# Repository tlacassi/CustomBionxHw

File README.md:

# Custom BionX hardware

The original battery of my BionX e-bike is worn out. The new pack gets a DALY BMS with
balancing, and these boards replace what the original electronics did besides battery management.
Firmware: [BIONX_console_ESP32](https://github.com/tlacassi/BIONX_console_ESP32).

## How it works

Two ESP32-S3 boards linked by the bike's CAN bus.

- **Power Control** (near the battery): drives the motor, handles precharge, switching,
  sleep, current/voltage measurement and the link to the BMS.
- **Display** (handlebar): round screen, rotary encoder, brake and throttle inputs.

## Status

In progress.

- Power Control: routed (112 × 82 mm, 4 layers), **not manufactured yet**.
  The [audit](docs/AUDIT_PCB_POWER_CONTROL.md) (in French) lists issues to fix before ordering.
- Display: schematic only.

Designed in KiCad 10. Design choices and BOM in [`docs/`](docs/).

> Unvalidated prototype: do not manufacture or connect to a battery as is.

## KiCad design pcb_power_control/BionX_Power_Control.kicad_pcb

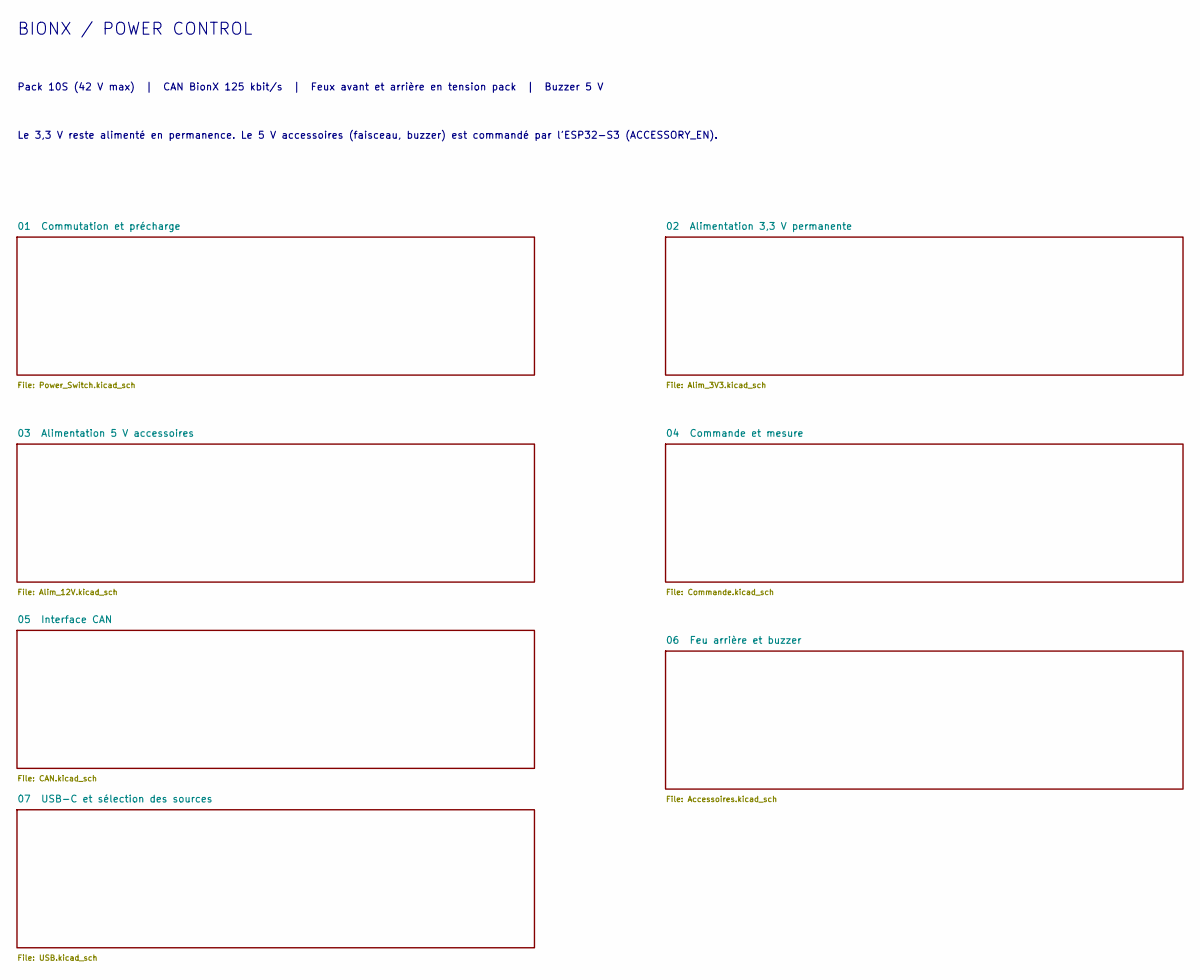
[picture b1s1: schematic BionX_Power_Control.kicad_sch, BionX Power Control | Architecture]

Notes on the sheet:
BIONX / POWER CONTROL
Pack 10S (42 V max) | CAN BionX 125 kbit/s | Feux avant et arrière en tension pack | Buzzer 5 V
Le 3,3 V reste alimenté en permanence. Le 5 V accessoires (faisceau, buzzer) est commandé par l'ESP32-S3 (ACCESSORY_EN).

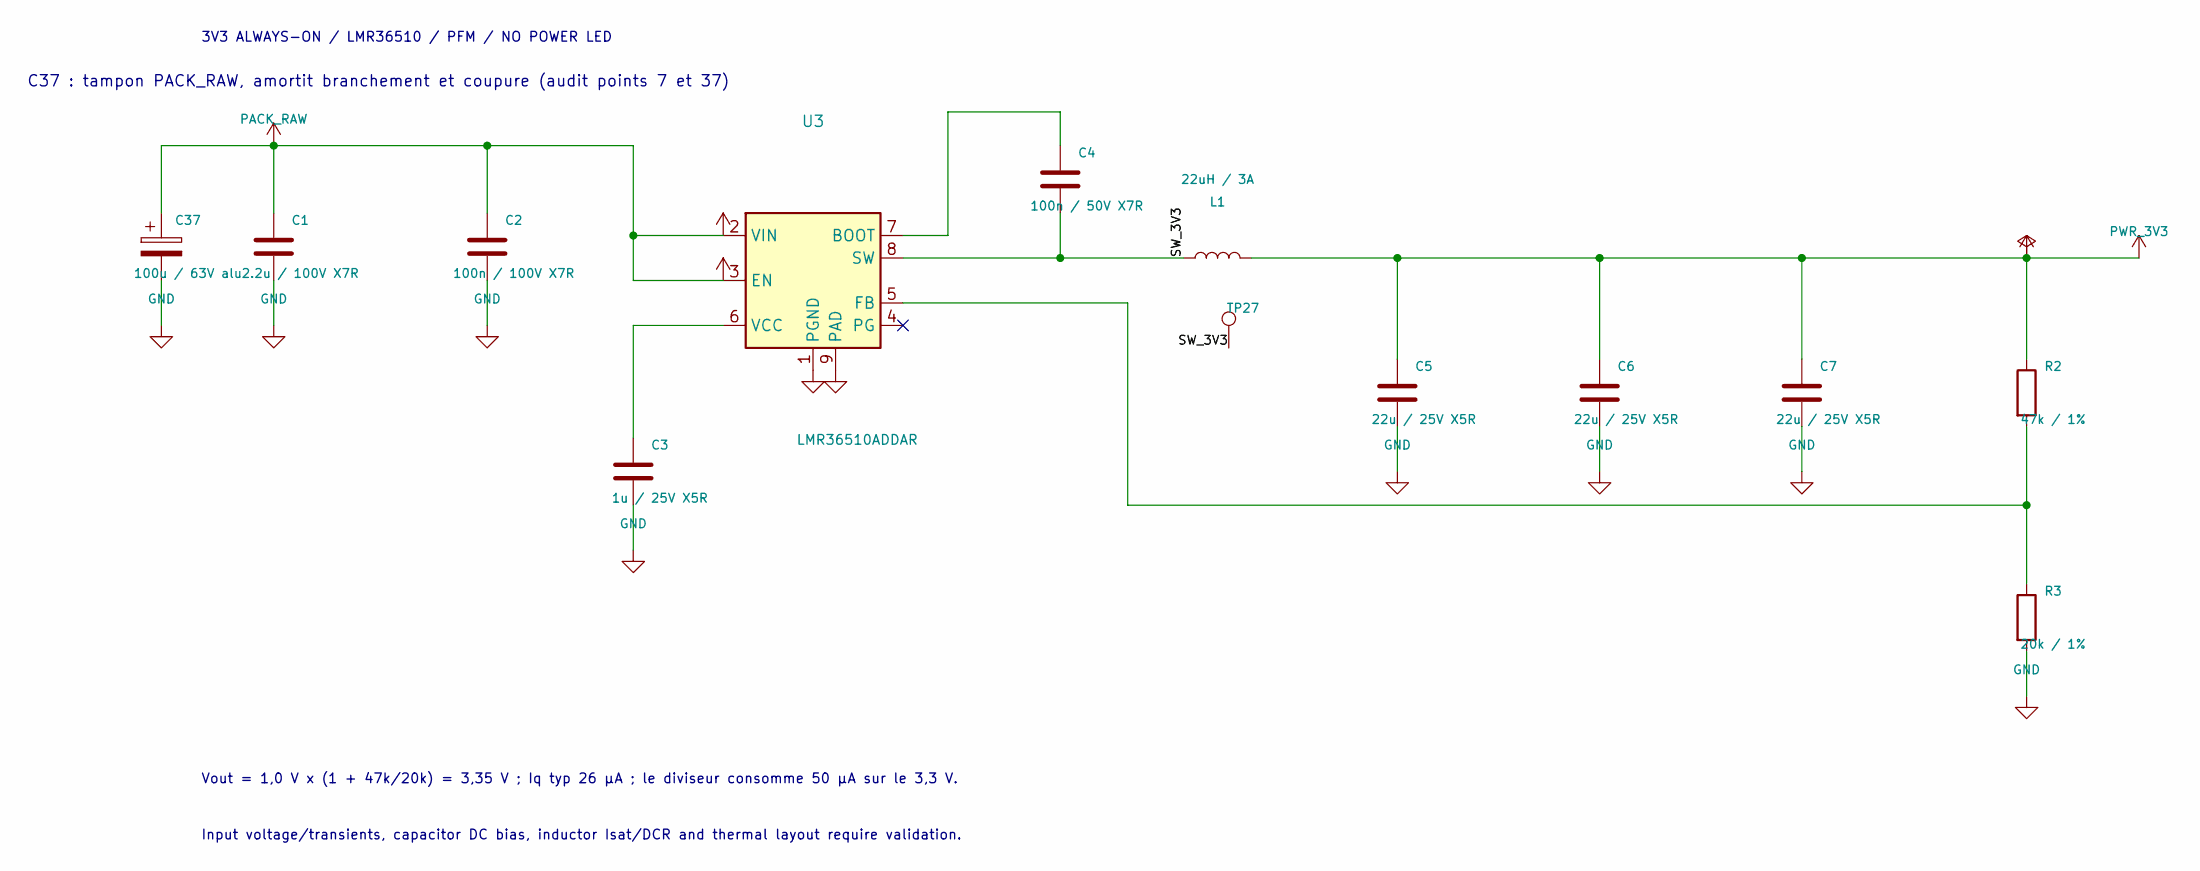
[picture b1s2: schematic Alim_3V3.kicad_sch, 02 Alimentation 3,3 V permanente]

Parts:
C1: 2.2u / 100V X7R; C_1210_3225Metric; MPN CL32B225KCJSNNE; LCSC C55151
C2: 100n / 100V X7R; C_0805_2012Metric; MPN CL21B104KCC5PNC; LCSC C472809
C3: 1u / 25V X5R; C_0402_1005Metric; MPN CL05A105KA5NQNC; LCSC C52923
C4: 100n / 50V X7R; C_0402_1005Metric; MPN CL05B104KB54PNC; LCSC C307331
C5, C6, C7: 22u / 25V X5R; C_1206_3216Metric; MPN CL31A226KAHNNNE; LCSC C12891
C37: 100u / 63V alu; CP_Elec_10x10.5; MPN CS1J101M-CRG10; LCSC C116430
L1: 22uH / 3A; L_Changjiang_FXL0630; MPN SRG0630-220-M; LCSC C53462993
R2: 47k / 1%; R_0603_1608Metric; MPN 0603WAF4702T5E; LCSC C25819
R3: 20k / 1%; R_0603_1608Metric; MPN 0603WAF2002T5E; LCSC C4184
TP27: SW_3V3; TestPoint_Pad_D1.0mm
U3: LMR36510ADDAR; HSOP-8-1EP_3.9x4.9mm_P1.27mm_EP2.41x3.1mm; MPN LMR36510ADDAR; LCSC C1858393

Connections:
/02 Alimentation 3,3 V permanente/SW_3V3: C4.2, L1.1, TP27.1, U3.8 (SW)
unnamed: C4.1, U3.7 (BOOT)
unnamed: R2.2, R3.1, U3.5 (FB)
unnamed: C3.1, U3.6 (VCC)
PWR_3V3: C5.1, C6.1, C7.1, L1.2, R2.1; also elsewhere on the board

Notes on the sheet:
Vout = 1,0 V x (1 + 47k/20k) = 3,35 V ; Iq typ 26 µA ; le diviseur consomme 50 µA sur le 3,3 V.
3V3 ALWAYS-ON / LMR36510 / PFM / NO POWER LED
Input voltage/transients, capacitor DC bias, inductor Isat/DCR and thermal layout require validation.
C37 : tampon PACK_RAW, amortit branchement et coupure (audit points 7 et 37)

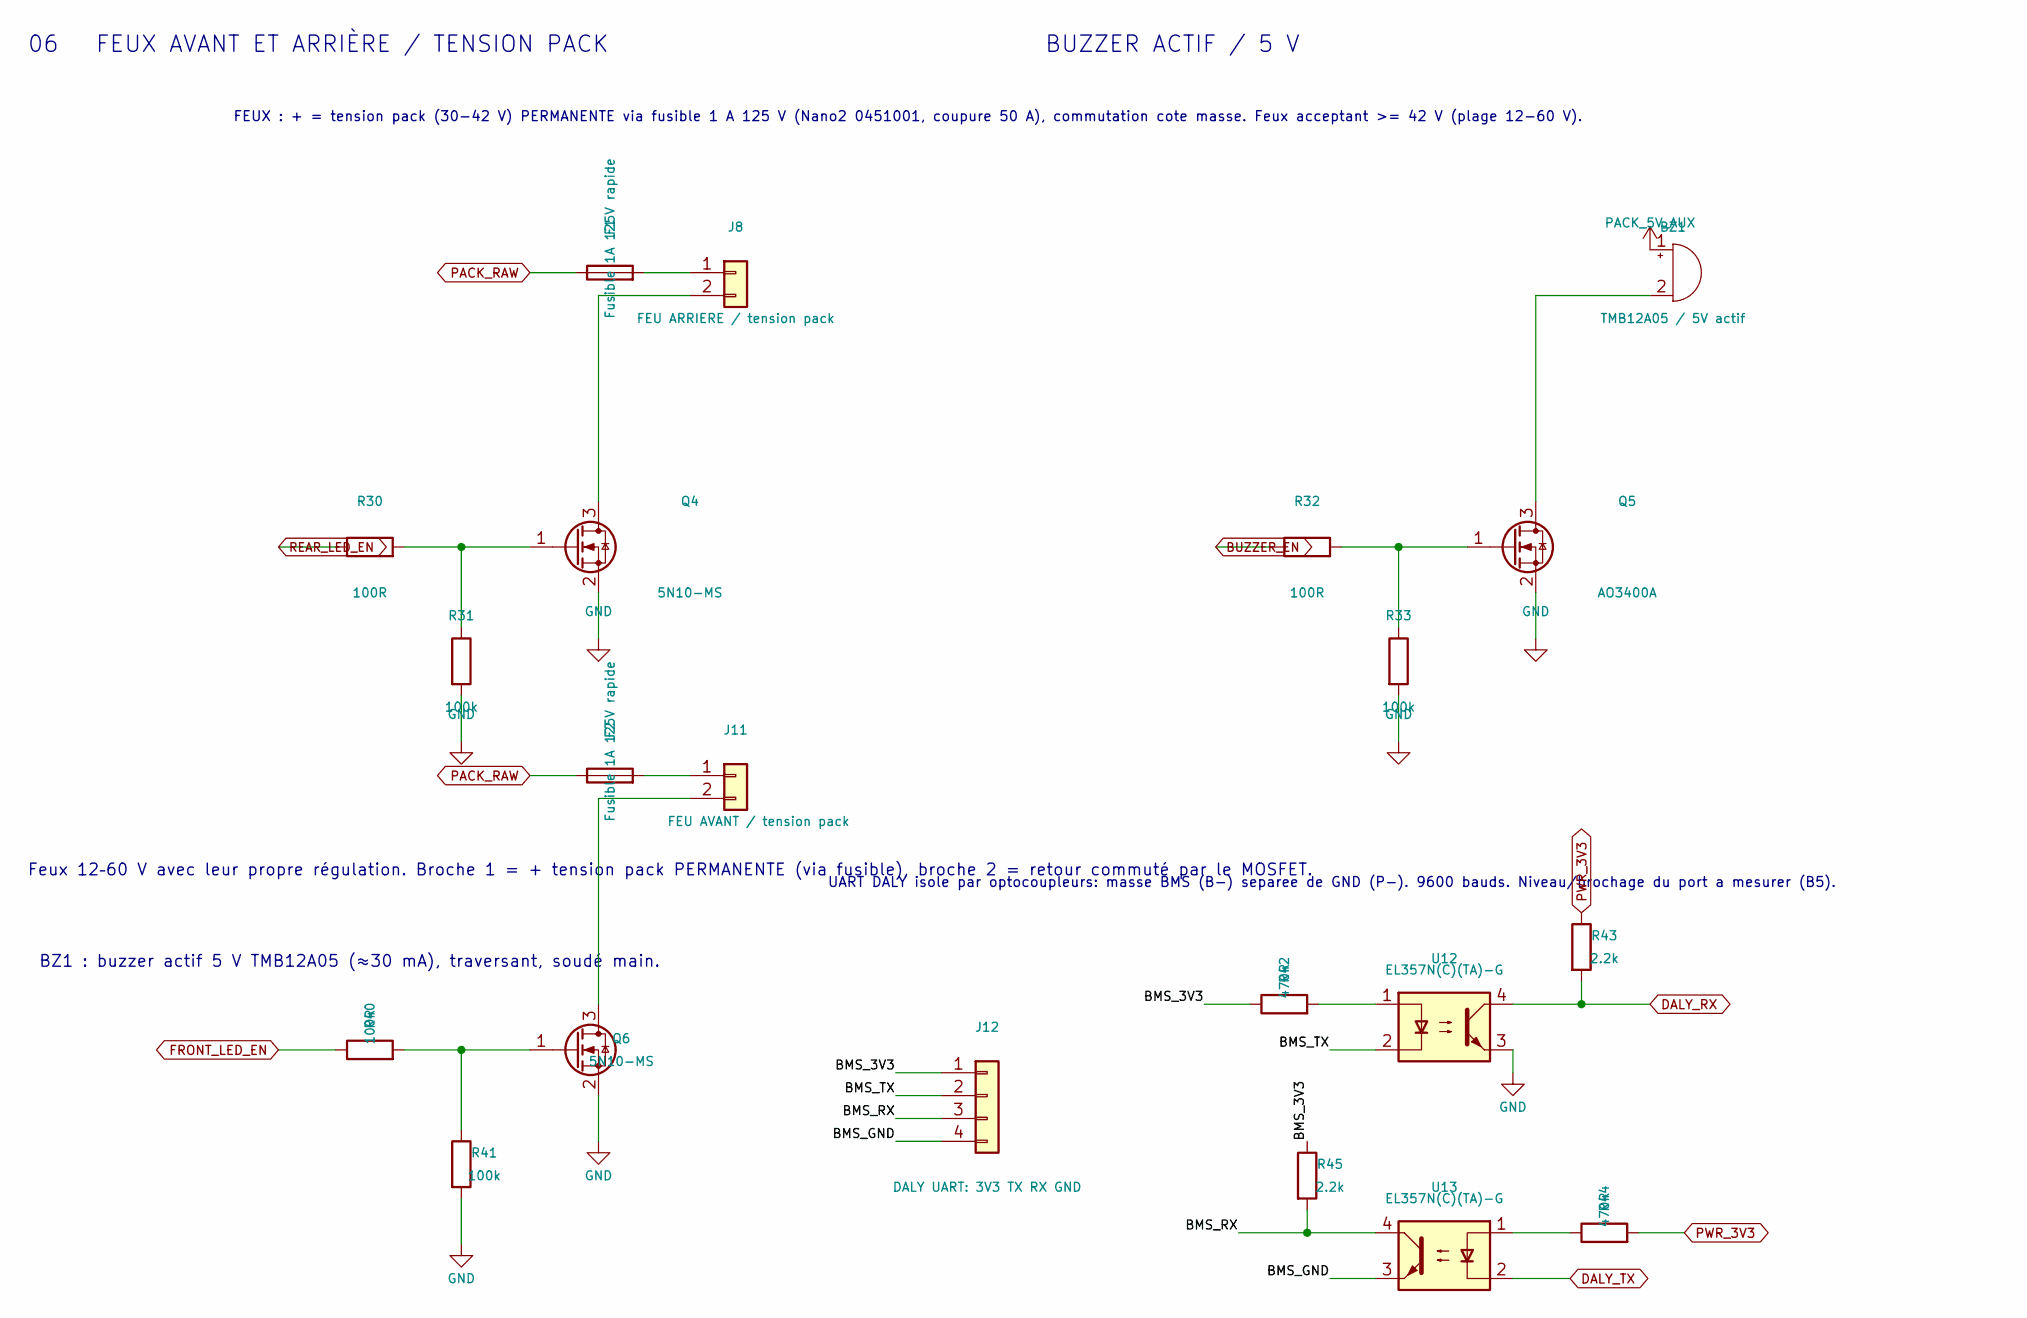
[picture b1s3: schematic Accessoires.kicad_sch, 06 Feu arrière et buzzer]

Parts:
BZ1: TMB12A05 / 5V actif; Buzzer_12x9.5RM7.6; MPN TMB12A05
F1, F2: Fusible 1A 125V rapide; Fuse_Littelfuse-NANO2-451_453; MPN 0451001.MRL; LCSC C3099
J8: FEU ARRIERE / tension pack; JST_XH_B2B-XH-A_1x02_P2.50mm_Vertical; MPN B2B-XH-A
J11: FEU AVANT / tension pack; JST_XH_B2B-XH-A_1x02_P2.50mm_Vertical; MPN B2B-XH-A
J12: DALY UART: 3V3 TX RX GND; JST_XH_B4B-XH-A_1x04_P2.50mm_Vertical; MPN B4B-XH-A
Q4, Q6: 5N10-MS; SOT-23; MPN 5N10-MS; LCSC C5140036
Q5: AO3400A; SOT-23; MPN AO3400A; LCSC C20917
R30, R32, R40: 100R; R_0603_1608Metric; MPN 0603WAF1000T5E; LCSC C22775
R31, R33, R41: 100k; R_0603_1608Metric; MPN 0603WAF1003T5E; LCSC C25803
R42, R44: 470R; R_0603_1608Metric; MPN 0603WAF4700T5E; LCSC C23179
R43, R45: 2.2k; R_0603_1608Metric; MPN 0603WAF2201T5E; LCSC C4190
U12, U13: EL357N(C)(TA)-G; SOP-4_EL357N_Everlight; MPN EL357N(C)(TA)-G; LCSC C42379244

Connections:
/06 Feu arrière et buzzer/BMS_3V3: J12.1, R42.1, R45.1
/06 Feu arrière et buzzer/BMS_GND: J12.4, U13.3
/06 Feu arrière et buzzer/BMS_RX: J12.3, R45.2, U13.4
/06 Feu arrière et buzzer/BMS_TX: J12.2, U12.2
BUZZER_EN: R32.1; also elsewhere on the board
DALY_RX: R43.2, U12.4; also elsewhere on the board
DALY_TX: U13.2; also elsewhere on the board
FRONT_LED_EN: R40.1; also elsewhere on the board
unnamed: BZ1.2 (-), Q5.3 (D)
unnamed: F1.2, J8.1
unnamed: J8.2, Q4.3 (D)
unnamed: F2.2, J11.1
unnamed: J11.2, Q6.3 (D)
unnamed: Q4.1 (G), R30.2, R31.1
unnamed: Q5.1 (G), R32.2, R33.1
unnamed: Q6.1 (G), R40.2, R41.1
unnamed: R42.2, U12.1
unnamed: R44.1, U13.1
PACK_5V_AUX: BZ1.1 (+); also elsewhere on the board
PWR_3V3: R43.1, R44.2; also elsewhere on the board
REAR_LED_EN: R30.1; also elsewhere on the board

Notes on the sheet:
BUZZER ACTIF / 5 V
BZ1 : buzzer actif 5 V TMB12A05 (≈30 mA), traversant, soudé main.
Feux 12–60 V avec leur propre régulation. Broche 1 = + tension pack PERMANENTE (via fusible), broche 2 = retour commuté par le MOSFET.
06 FEUX AVANT ET ARRIÈRE / TENSION PACK
UART DALY isole par optocoupleurs: masse BMS (B-) separee de GND (P-). 9600 bauds. Niveau/brochage du port a mesurer (B5).
FEUX : + = tension pack (30-42 V) PERMANENTE via fusible 1 A 125 V (Nano2 0451001, coupure 50 A), commutation cote masse. Feux acceptant >= 42 V (plage 12-60 V).

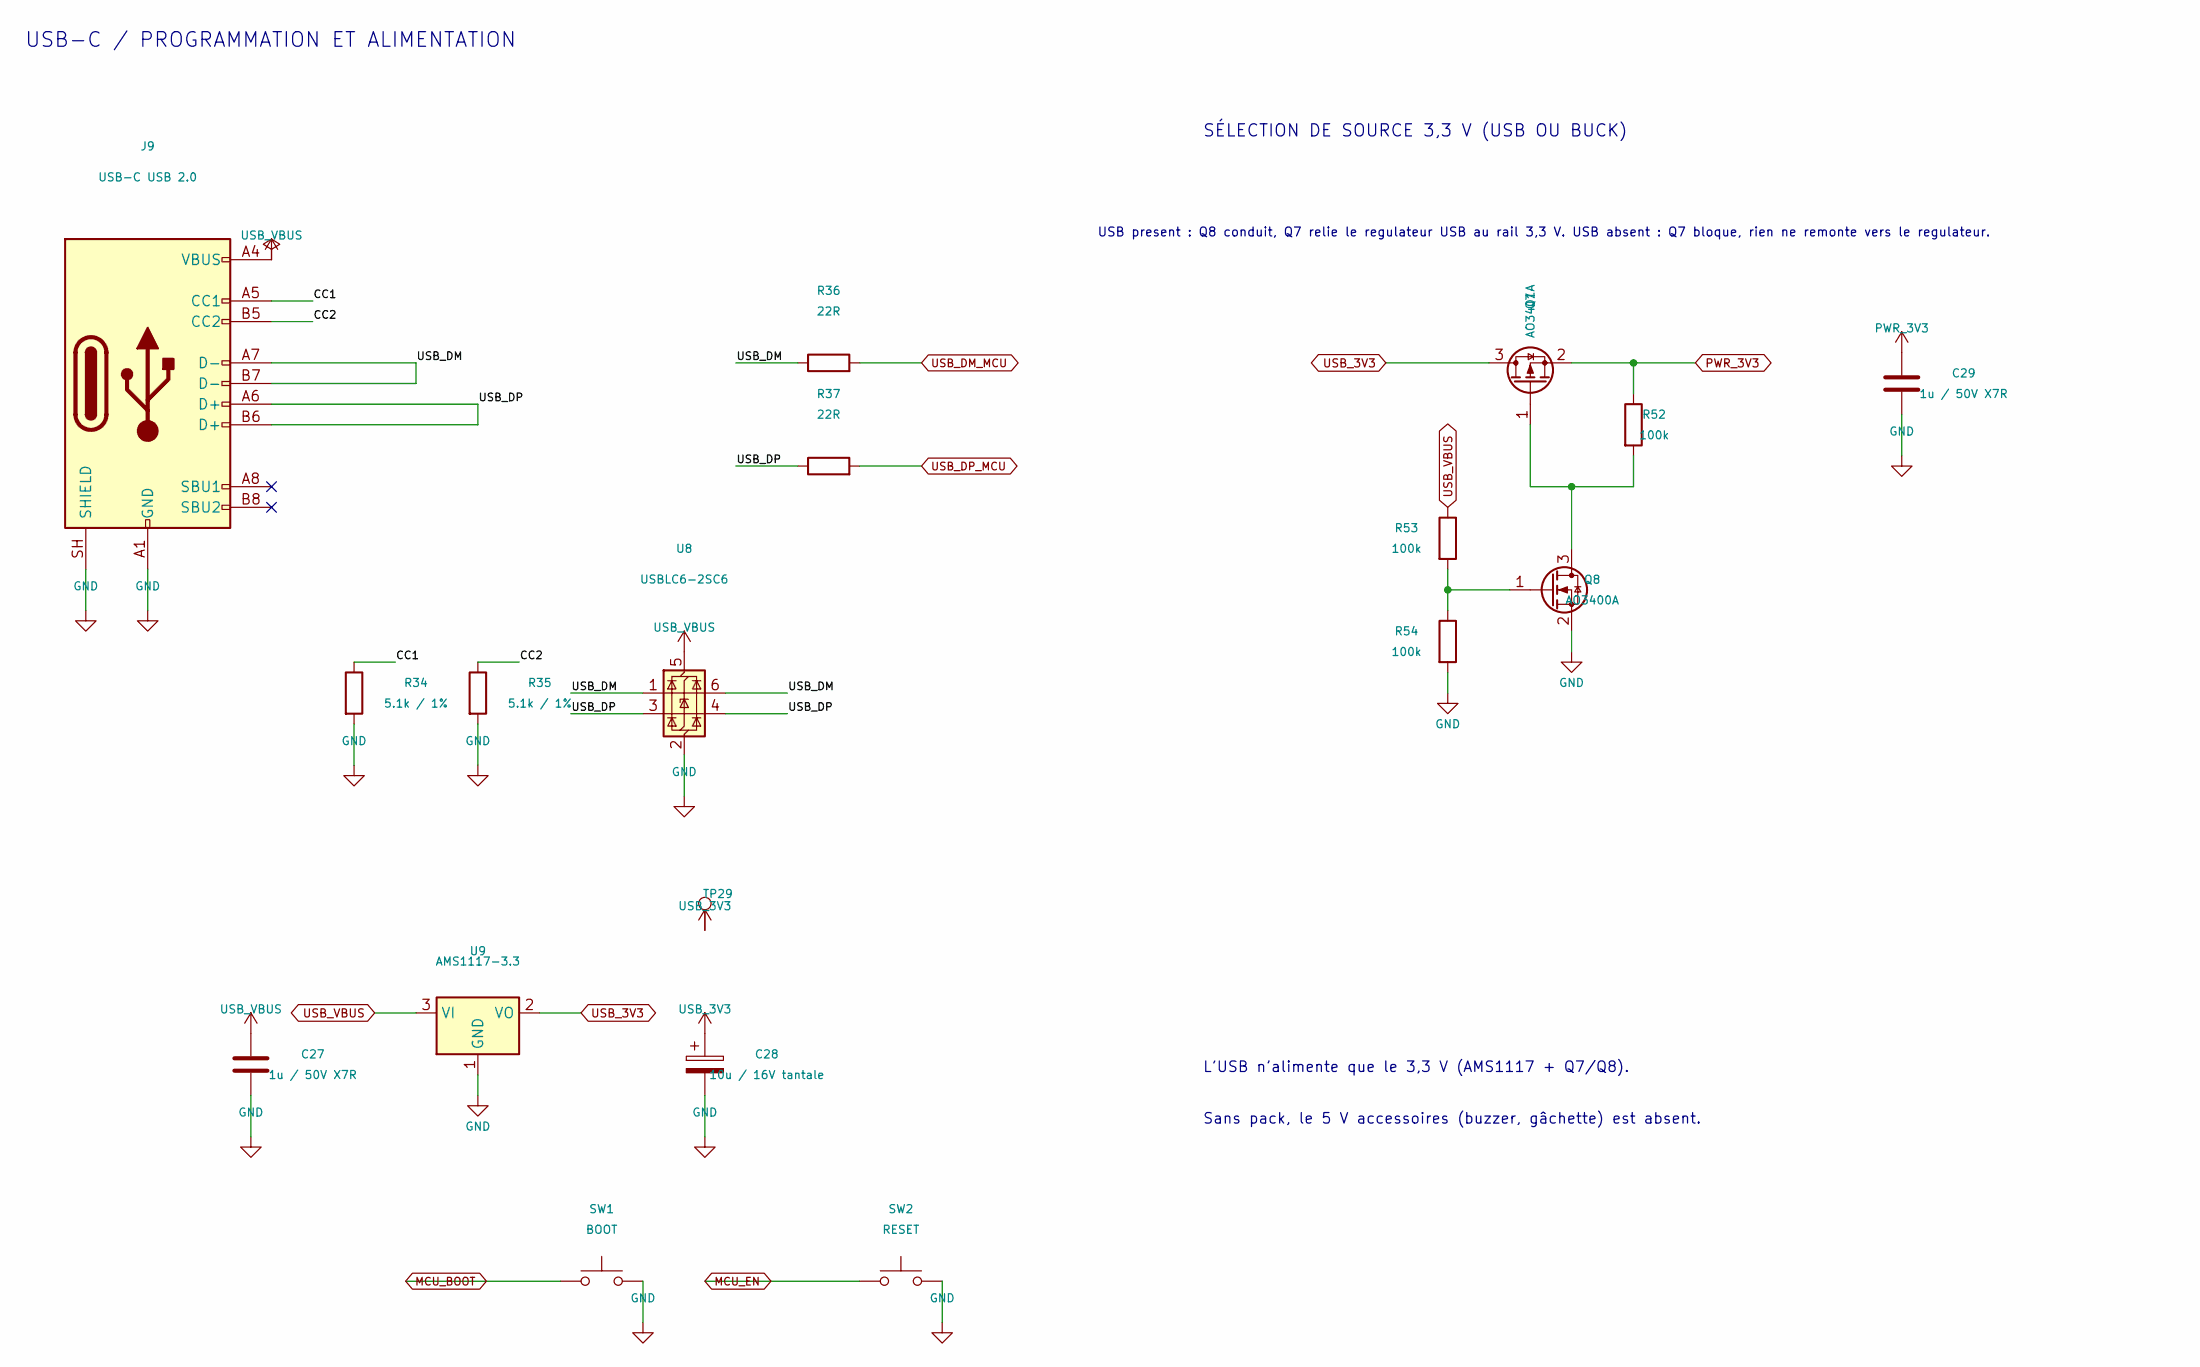
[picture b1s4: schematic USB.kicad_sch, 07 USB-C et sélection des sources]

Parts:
C27, C29: 1u / 50V X7R; C_0805_2012Metric; MPN CL21B105KBFNNNE; LCSC C28323
C28: 10u / 16V tantale; CP_EIA-3216-18_Kemet-A; MPN TAJA106K016RNJ; LCSC C7171
J9: USB-C USB 2.0; USB_C_Receptacle_HRO_TYPE-C-31-M-12; MPN TYPE-C-31-M-12; LCSC C165948
Q7: AO3401A; SOT-23; MPN AO3401A; LCSC C15127
Q8: AO3400A; SOT-23; MPN AO3400A; LCSC C20917
R34, R35: 5.1k / 1%; R_0603_1608Metric; MPN 0603WAF5101T5E; LCSC C23186
R36, R37: 22R; R_0603_1608Metric; MPN 0603WAF220JT5E; LCSC C23345
R52, R53, R54: 100k; R_0603_1608Metric; MPN 0603WAF1003T5E; LCSC C25803
SW1: BOOT; SW_Push_1P1T_XKB_TS-1187A; MPN TS-1187A-B-A-B; LCSC C318884
SW2: RESET; SW_Push_1P1T_XKB_TS-1187A; MPN TS-1187A-B-A-B; LCSC C318884
TP29: USB_3V3; TestPoint_Pad_D1.0mm
U8: USBLC6-2SC6; SOT-23-6; MPN USBLC6-2SC6; LCSC C7519
U9: AMS1117-3.3; SOT-223-3_TabPin2; MPN AMS1117-3.3; LCSC C6186

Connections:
/07 USB-C et sélection des sources/CC1: J9.A5 (CC1), R34.1
/07 USB-C et sélection des sources/CC2: J9.B5 (CC2), R35.1
/07 USB-C et sélection des sources/USB_DM: J9.A7 (D-), J9.B7 (D-), R36.1, U8.1 (I/O1), U8.6 (I/O1)
/07 USB-C et sélection des sources/USB_DP: J9.A6 (D+), J9.B6 (D+), R37.1, U8.3 (I/O2), U8.4 (I/O2)
MCU_BOOT: SW1.1; also elsewhere on the board
MCU_EN: SW2.1; also elsewhere on the board
unnamed: Q7.1 (G), Q8.3 (D), R52.2
unnamed: Q8.1 (G), R53.2, R54.1
PWR_3V3: C29.1, Q7.2 (S), R52.1; also elsewhere on the board
USB_3V3: C28.1, Q7.3 (D), TP29.1, U9.2 (VO)
USB_DM_MCU: R36.2; also elsewhere on the board
USB_DP_MCU: R37.2; also elsewhere on the board
USB_VBUS: C27.1, J9.A4 (VBUS), J9.A9 (VBUS), J9.B4 (VBUS), J9.B9 (VBUS), R53.1, U8.5 (VBUS), U9.3 (VI); also elsewhere on the board

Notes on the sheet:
USB-C / PROGRAMMATION ET ALIMENTATION
SÉLECTION DE SOURCE 3,3 V (USB OU BUCK)
L'USB n'alimente que le 3,3 V (AMS1117 + Q7/Q8).
Sans pack, le 5 V accessoires (buzzer, gâchette) est absent.
USB present : Q8 conduit, Q7 relie le regulateur USB au rail 3,3 V. USB absent : Q7 bloque, rien ne remonte vers le regulateur.

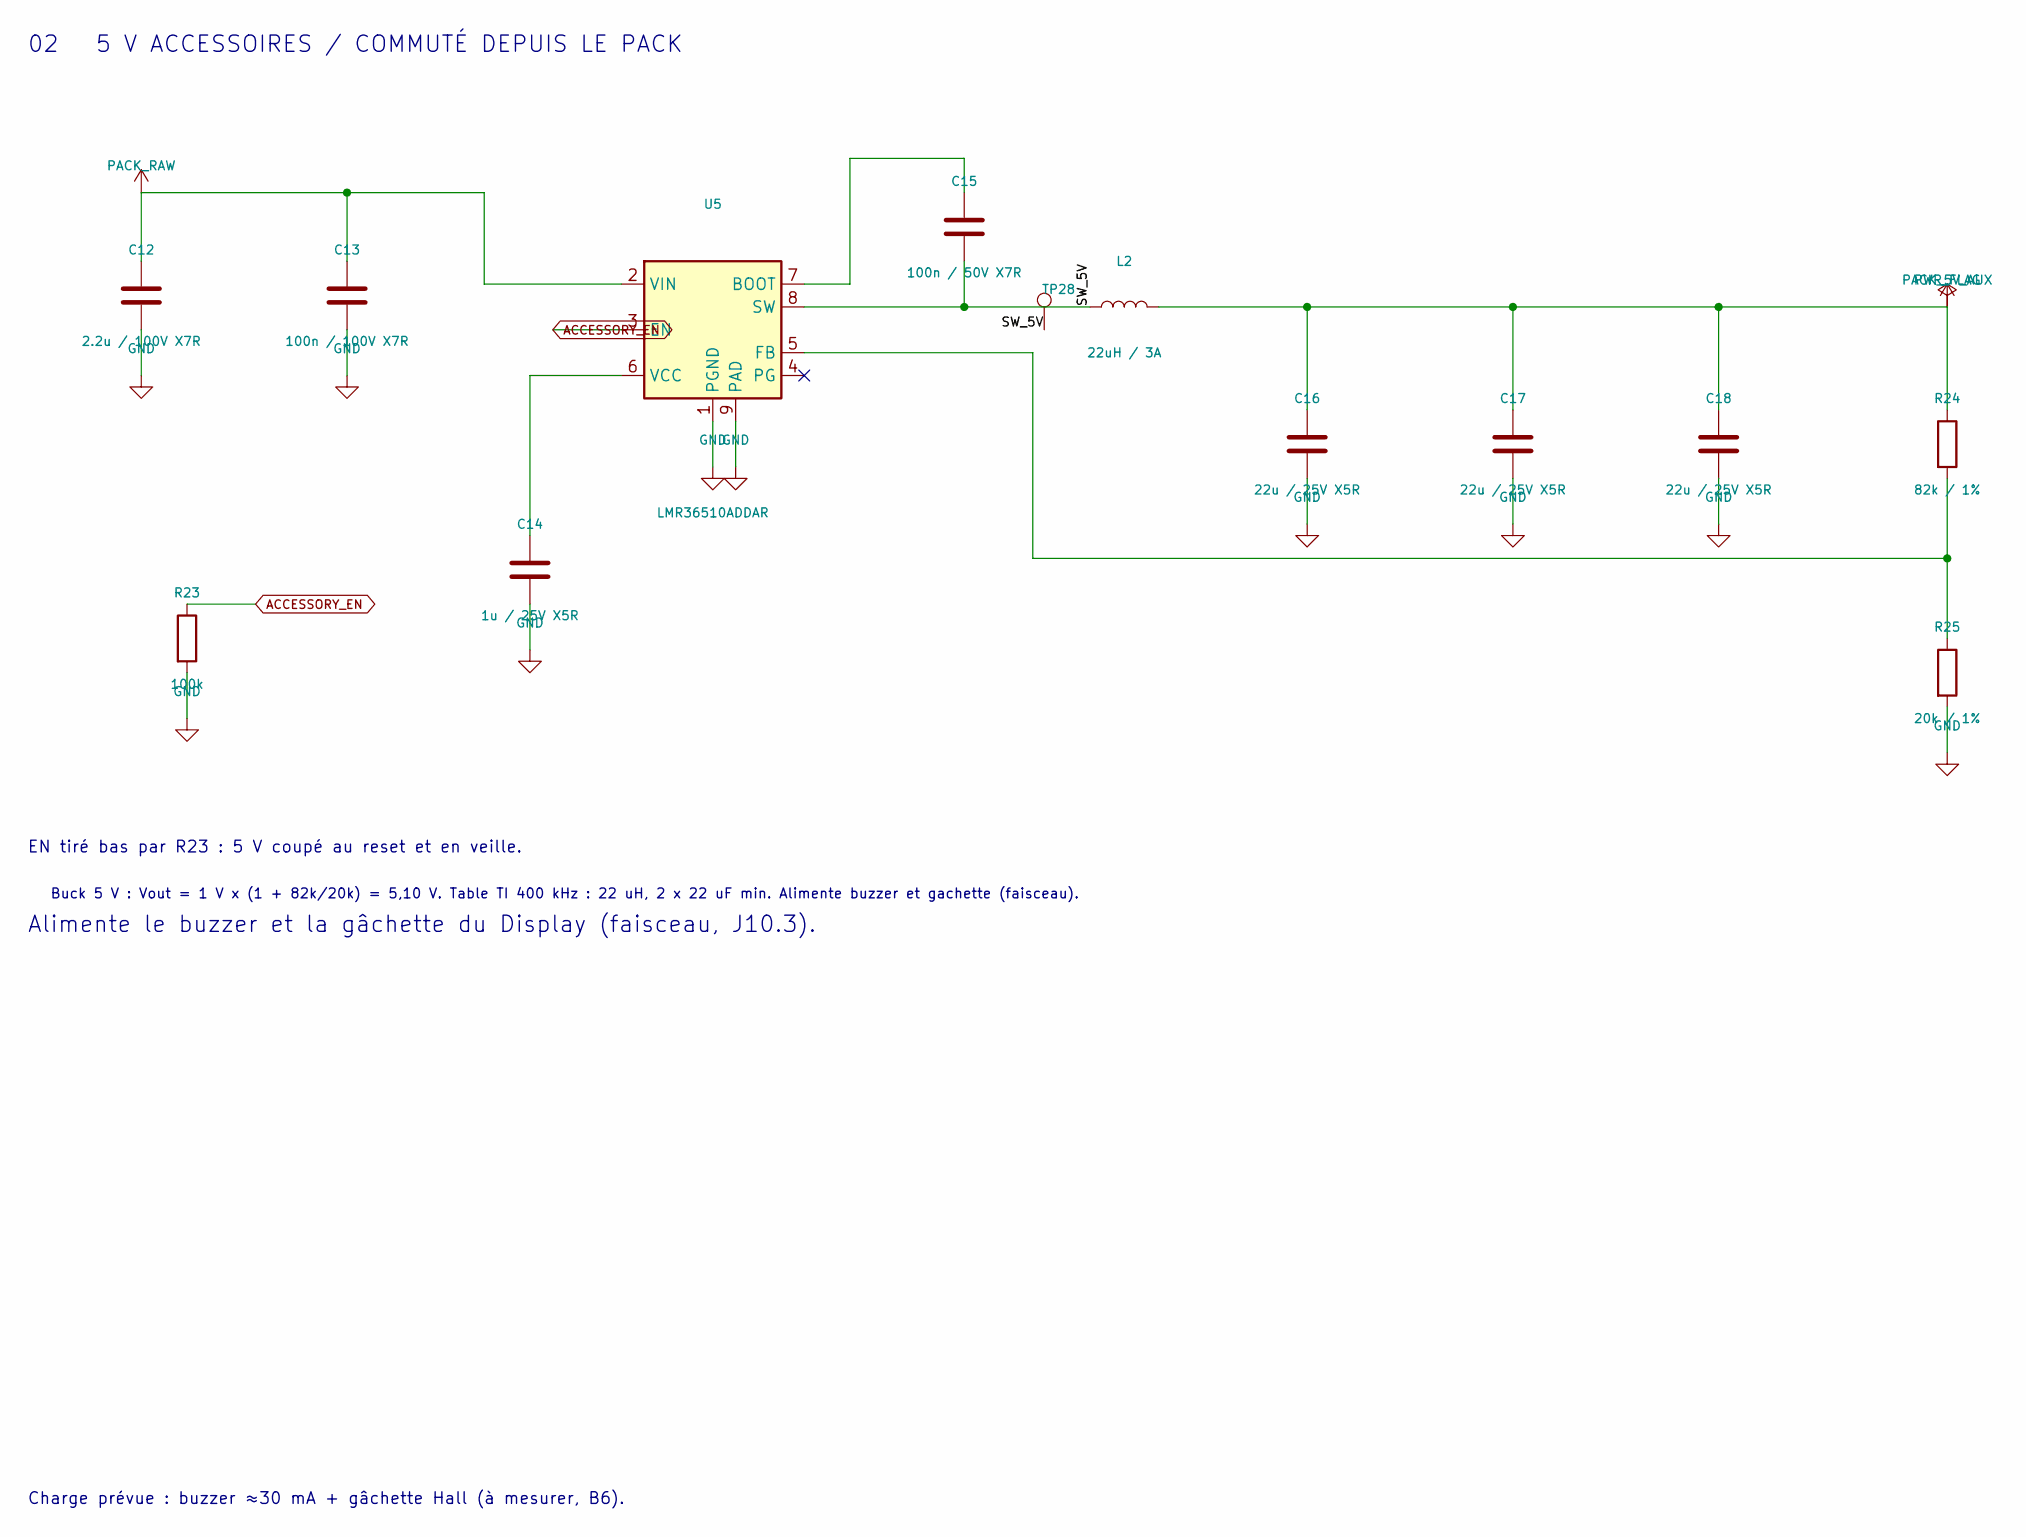
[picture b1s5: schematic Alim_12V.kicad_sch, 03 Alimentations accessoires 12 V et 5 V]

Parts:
C12: 2.2u / 100V X7R; C_1210_3225Metric; MPN CL32B225KCJSNNE; LCSC C55151
C13: 100n / 100V X7R; C_0805_2012Metric; MPN CL21B104KCC5PNC; LCSC C472809
C14: 1u / 25V X5R; C_0402_1005Metric; MPN CL05A105KA5NQNC; LCSC C52923
C15: 100n / 50V X7R; C_0402_1005Metric; MPN CL05B104KB54PNC; LCSC C307331
C16, C17, C18: 22u / 25V X5R; C_1206_3216Metric; MPN CL31A226KAHNNNE; LCSC C12891
L2: 22uH / 3A; L_Changjiang_FXL0630; MPN SRG0630-220-M; LCSC C53462993
R23: 100k; R_0603_1608Metric; MPN 0603WAF1003T5E; LCSC C25803
R24: 82k / 1%; R_0603_1608Metric; MPN 0603WAF8202T5E; LCSC C23254
R25: 20k / 1%; R_0603_1608Metric; MPN 0603WAF2002T5E; LCSC C4184
TP28: SW_5V; TestPoint_Pad_D1.0mm
U5: LMR36510ADDAR; HSOP-8-1EP_3.9x4.9mm_P1.27mm_EP2.41x3.1mm; MPN LMR36510ADDAR; LCSC C1858393

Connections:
/03 Alimentation 5 V accessoires/SW_5V: C15.2, L2.1, TP28.1, U5.8 (SW)
ACCESSORY_EN: R23.1, U5.3 (EN); also elsewhere on the board
unnamed: C15.1, U5.7 (BOOT)
unnamed: R24.2, R25.1, U5.5 (FB)
unnamed: C14.1, U5.6 (VCC)
PACK_5V_AUX: C16.1, C17.1, C18.1, L2.2, R24.1; also elsewhere on the board

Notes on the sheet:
02 5 V ACCESSOIRES / COMMUTÉ DEPUIS LE PACK
Alimente le buzzer et la gâchette du Display (faisceau, J10.3).
Charge prévue : buzzer ≈30 mA + gâchette Hall (à mesurer, B6).
EN tiré bas par R23 : 5 V coupé au reset et en veille.
Buck 5 V : Vout = 1 V x (1 + 82k/20k) = 5,10 V. Table TI 400 kHz : 22 uH, 2 x 22 uF min. Alimente buzzer et gachette (faisceau).

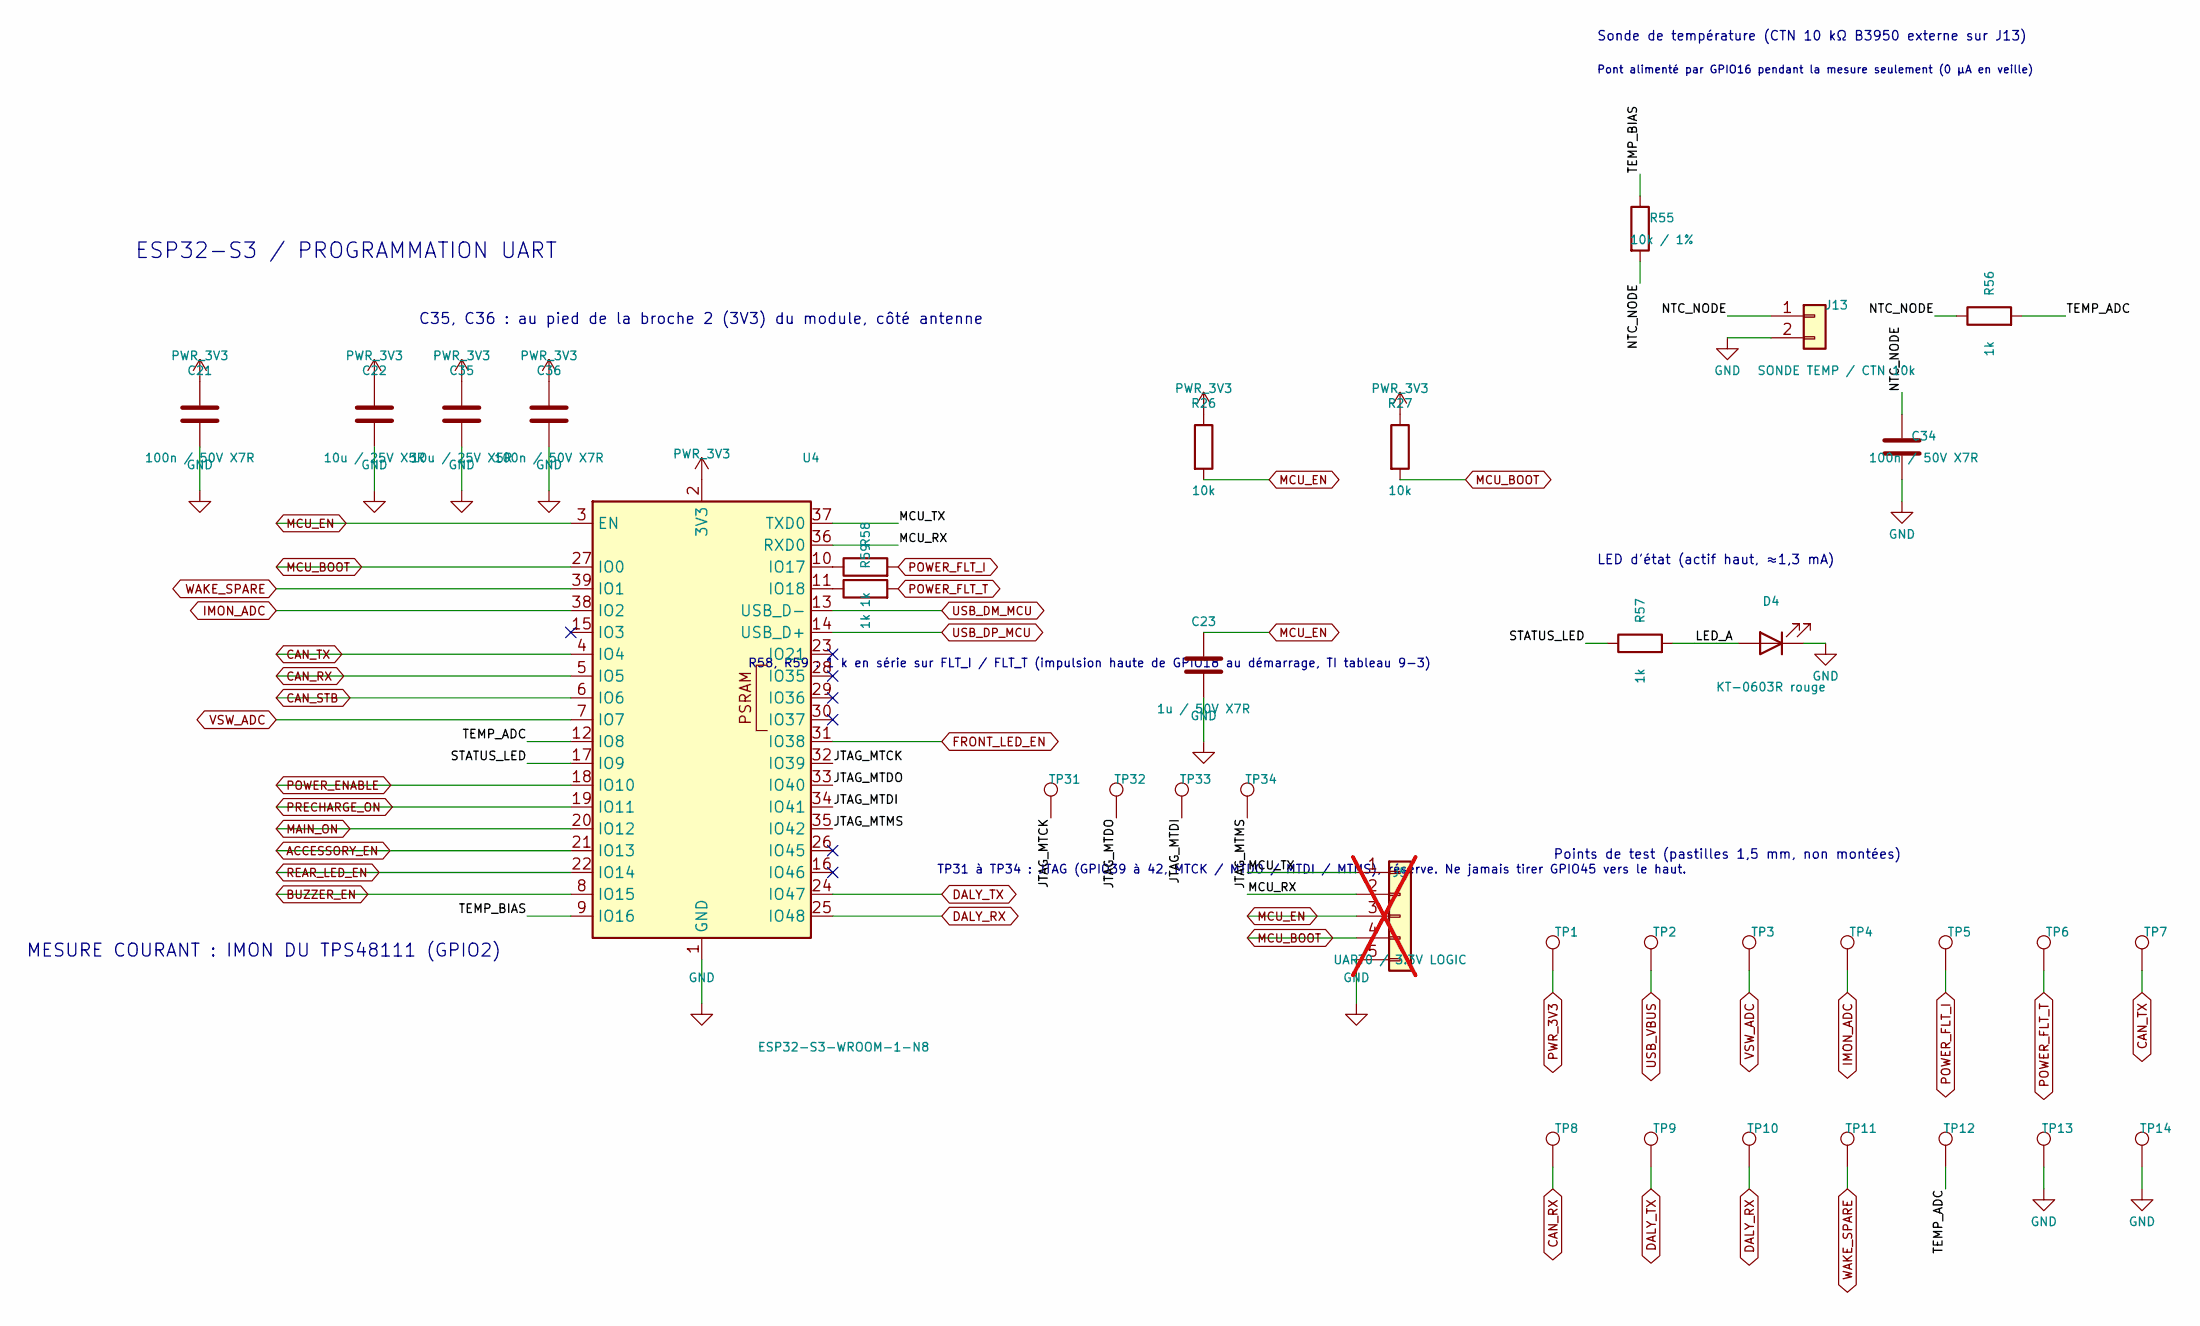
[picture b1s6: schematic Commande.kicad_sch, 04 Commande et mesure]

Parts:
C21: 100n / 50V X7R; C_0805_2012Metric; MPN CC0805KRX7R9BB104; LCSC C49678
C22, C35: 10u / 25V X5R; C_0805_2012Metric; MPN CL21A106KAYNNNE; LCSC C15850
C23: 1u / 50V X7R; C_0805_2012Metric; MPN CL21B105KBFNNNE; LCSC C28323
C34, C36: 100n / 50V X7R; C_0603_1608Metric; MPN CC0603KRX7R9BB104; LCSC C14663
D4: KT-0603R rouge; LED_0603_1608Metric; MPN KT-0603R; LCSC C2286
J5: UART0 / 3.3V LOGIC; PinHeader_1x05_P2.54mm_Vertical; not fitted
J13: SONDE TEMP / CTN 10k; JST_XH_B2B-XH-A_1x02_P2.50mm_Vertical; MPN B2B-XH-A
R26, R27: 10k; R_0603_1608Metric; MPN 0603WAF1002T5E; LCSC C25804
R55: 10k / 1%; R_0603_1608Metric; MPN 0603WAF1002T5E; LCSC C25804
R56, R57: 1k; R_0603_1608Metric; MPN 0603WAF1001T5E; LCSC C21190
R58, R59: 1k; R_0402_1005Metric; MPN 0402WGF1001TCE; LCSC C11702
TP1: PWR_3V3; TestPoint_Pad_D1.5mm
TP2: USB_VBUS; TestPoint_Pad_D1.5mm
TP3: VSW_ADC; TestPoint_Pad_D1.5mm
TP4: IMON_ADC; TestPoint_Pad_D1.5mm
TP5: POWER_FLT_I; TestPoint_Pad_D1.5mm
TP6: POWER_FLT_T; TestPoint_Pad_D1.5mm
TP7: CAN_TX; TestPoint_Pad_D1.5mm
TP8: CAN_RX; TestPoint_Pad_D1.5mm
TP9: DALY_TX; TestPoint_Pad_D1.5mm
TP10: DALY_RX; TestPoint_Pad_D1.5mm
TP11: WAKE_SPARE; TestPoint_Pad_D1.5mm
TP12: TEMP_ADC; TestPoint_Pad_D1.5mm
TP13, TP14: GND; TestPoint_Pad_D1.5mm
TP31: JTAG_MTCK; TestPoint_Pad_D1.0mm
TP32: JTAG_MTDO; TestPoint_Pad_D1.0mm
TP33: JTAG_MTDI; TestPoint_Pad_D1.0mm
TP34: JTAG_MTMS; TestPoint_Pad_D1.0mm
U4: ESP32-S3-WROOM-1-N8; ESP32-S3-WROOM-1; MPN ESP32-S3-WROOM-1-N8; LCSC C2913198

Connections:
/04 Commande et mesure/JTAG_MTCK: TP31.1, U4.32 (IO39)
/04 Commande et mesure/JTAG_MTDI: TP33.1, U4.34 (IO41)
/04 Commande et mesure/JTAG_MTDO: TP32.1, U4.33 (IO40)
/04 Commande et mesure/JTAG_MTMS: TP34.1, U4.35 (IO42)
/04 Commande et mesure/LED_A: D4.2 (A), R57.2
/04 Commande et mesure/MCU_RX: J5.2, U4.36 (RXD0)
/04 Commande et mesure/MCU_TX: J5.1, U4.37 (TXD0)
/04 Commande et mesure/NTC_NODE: C34.1, J13.1, R55.2, R56.1
/04 Commande et mesure/STATUS_LED: R57.1, U4.17 (IO9)
/04 Commande et mesure/TEMP_ADC: R56.2, TP12.1, U4.12 (IO8)
/04 Commande et mesure/TEMP_BIAS: R55.1, U4.9 (IO16)
ACCESSORY_EN: U4.21 (IO13); also elsewhere on the board
BUZZER_EN: U4.8 (IO15); also elsewhere on the board
CAN_RX: TP8.1, U4.5 (IO5); also elsewhere on the board
CAN_STB: U4.6 (IO6); also elsewhere on the board
CAN_TX: TP7.1, U4.4 (IO4); also elsewhere on the board
DALY_RX: TP10.1, U4.25 (IO48); also elsewhere on the board
DALY_TX: TP9.1, U4.24 (IO47); also elsewhere on the board
FRONT_LED_EN: U4.31 (IO38); also elsewhere on the board
IMON_ADC: TP4.1, U4.38 (IO2); also elsewhere on the board
MAIN_ON: U4.20 (IO12); also elsewhere on the board
MCU_BOOT: J5.4, R27.2, U4.27 (IO0); also elsewhere on the board
MCU_EN: C23.1, J5.3, R26.2, U4.3 (EN); also elsewhere on the board
unnamed: R58.1, U4.10 (IO17)
unnamed: R59.1, U4.11 (IO18)
POWER_ENABLE: U4.18 (IO10); also elsewhere on the board
POWER_FLT_I: R58.2, TP5.1; also elsewhere on the board
POWER_FLT_T: R59.2, TP6.1; also elsewhere on the board
PRECHARGE_ON: U4.19 (IO11); also elsewhere on the board
PWR_3V3: C21.1, C22.1, C35.1, C36.1, R26.1, R27.1, TP1.1, U4.2 (3V3); also elsewhere on the board
REAR_LED_EN: U4.22 (IO14); also elsewhere on the board
USB_DM_MCU: U4.13 (USB_D-); also elsewhere on the board
USB_DP_MCU: U4.14 (USB_D+); also elsewhere on the board
USB_VBUS: TP2.1; also elsewhere on the board
VSW_ADC: TP3.1, U4.7 (IO7); also elsewhere on the board
WAKE_SPARE: TP11.1, U4.39 (IO1); also elsewhere on the board

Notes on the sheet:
ESP32-S3 / PROGRAMMATION UART
MESURE COURANT : IMON DU TPS48111 (GPIO2)
Sonde de température (CTN 10 kΩ B3950 externe sur J13)
Pont alimenté par GPIO16 pendant la mesure seulement (0 µA en veille)
LED d'état (actif haut, ≈1,3 mA)
Points de test (pastilles 1,5 mm, non montées)
C35, C36 : au pied de la broche 2 (3V3) du module, côté antenne
R58, R59 : 1 k en série sur FLT_I / FLT_T (impulsion haute de GPIO18 au démarrage, TI tableau 9-3)
TP31 à TP34 : JTAG (GPIO39 à 42, MTCK / MTDO / MTDI / MTMS), réserve. Ne jamais tirer GPIO45 vers le haut.
